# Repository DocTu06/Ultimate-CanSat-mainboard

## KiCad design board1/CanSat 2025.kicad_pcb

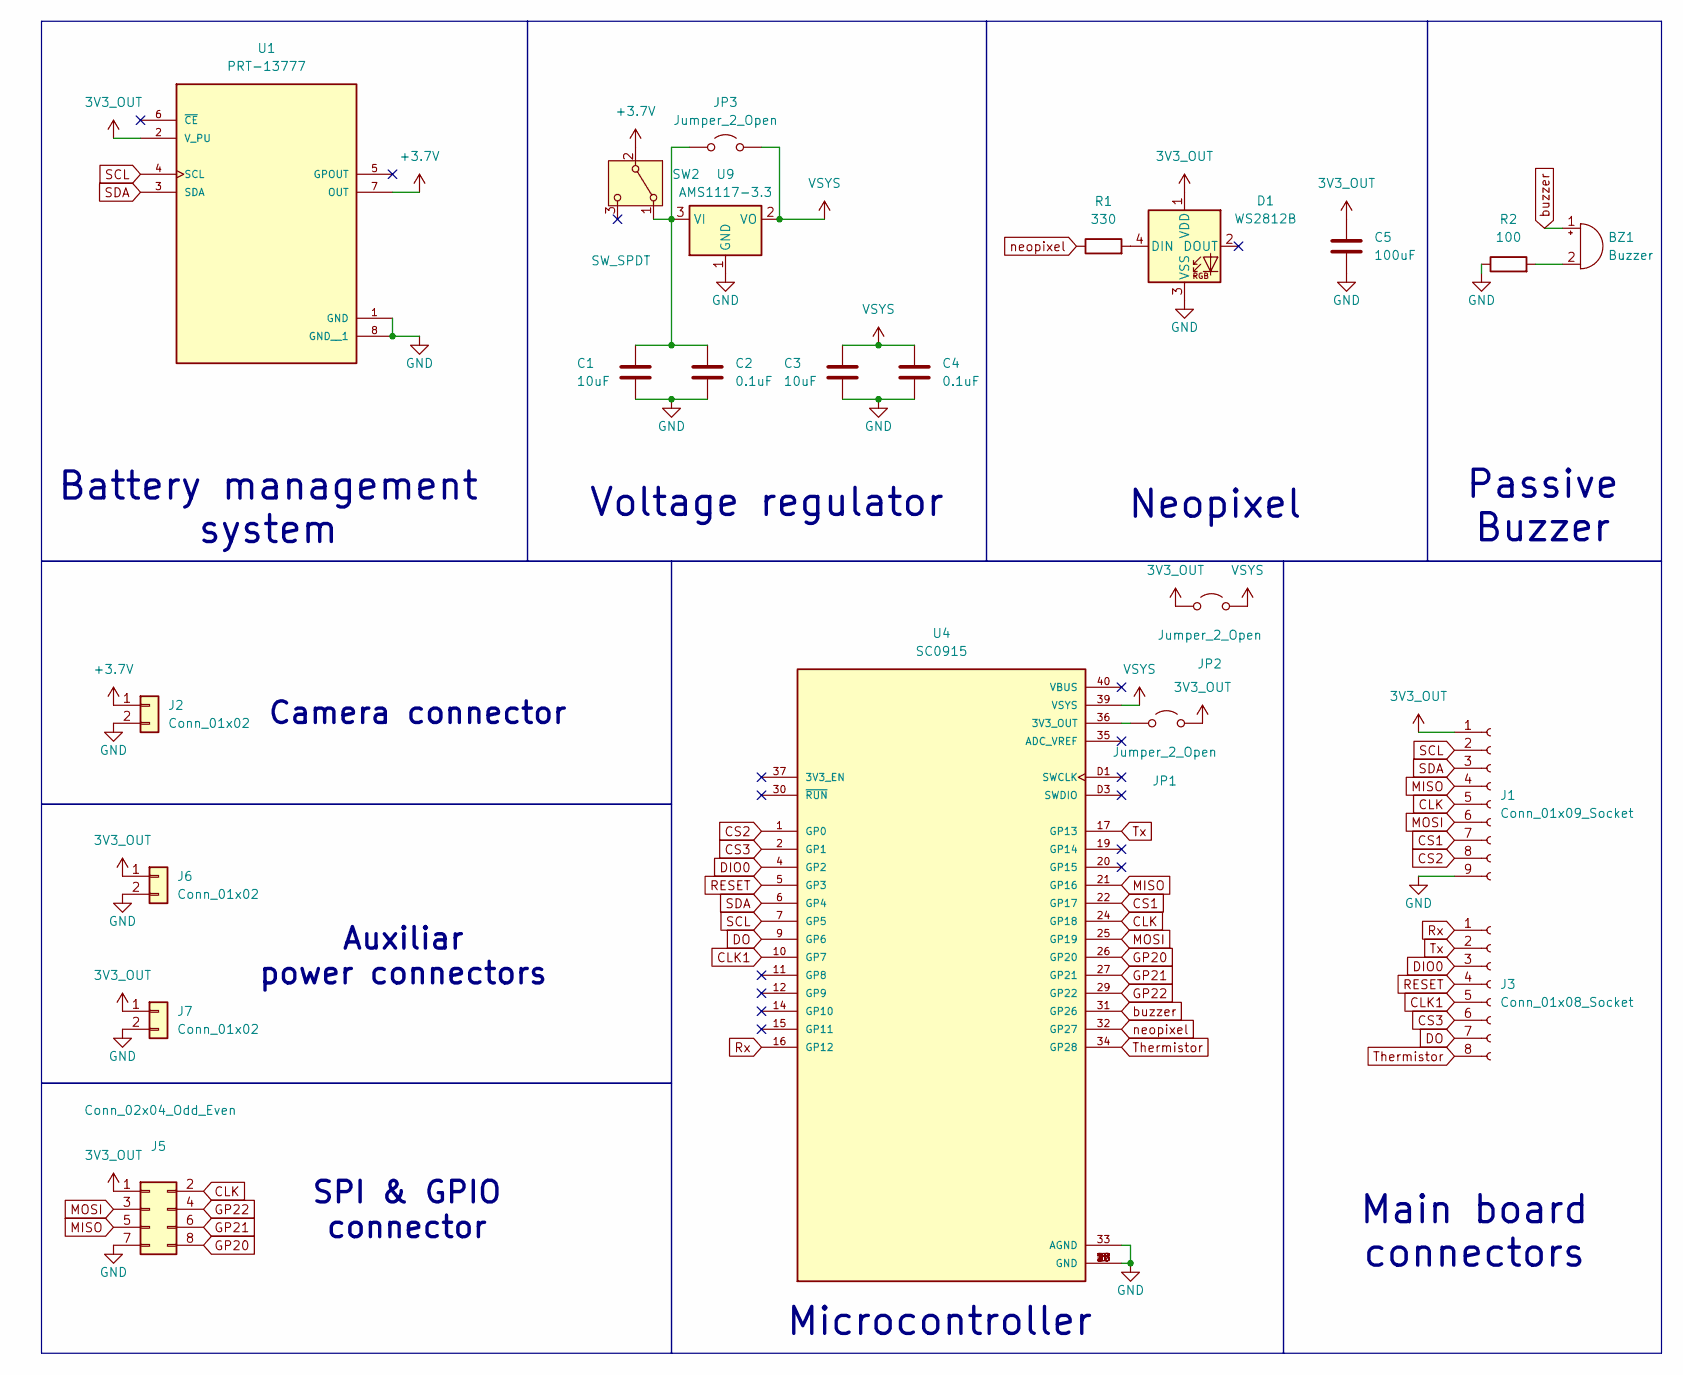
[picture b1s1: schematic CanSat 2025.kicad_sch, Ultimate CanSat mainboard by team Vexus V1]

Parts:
BZ1: Buzzer; Buzzer_pasiv
C1, C3: 10uF; C_0603_1608Metric_Pad1.08x0.95mm_HandSolder
C2, C4: 0.1uF; C_0603_1608Metric_Pad1.08x0.95mm_HandSolder
C5: 100uF; C_0603_1608Metric_Pad1.08x0.95mm_HandSolder
D1: WS2812B; LED_WS2812B_PLCC4_5.0x5.0mm_P3.2mm
J1: Conn_01x09_Socket; PinSocket_1x09_P2.54mm_Vertical
J2: Conn_01x02; Pad
J3: Conn_01x08_Socket; PinSocket_1x08_P2.54mm_Vertical
J5: Conn_02x04_Odd_Even; PinSocket_2x04_P2.54mm_Vertical
J6, J7: Conn_01x02; PinSocket_1x02_P2.54mm_Vertical
JP1, JP2, JP3: Jumper_2_Open; SolderJumper-2_P1.3mm_Open_TrianglePad1.0x1.5mm
R1: 330; R_0603_1608Metric_Pad0.98x0.95mm_HandSolder
R2: 100; R_0603_1608Metric_Pad0.98x0.95mm_HandSolder
SW2: SW_SPDT; SW_Slide_SPDT_Angled_CK_OS102011MA1Q
U1: PRT-13777; MODULE_PRT-13777; PARTREV v10
U4: SC0915; MODULE_SC0915; PARTREV 1.9
U9: AMS1117-3.3; SOT-223-3_TabPin2

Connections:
3V3_OUT: C5.1, D1.1 (VDD), J1.1, J5.1, J6.1, J7.1, JP1.2 (B), JP2.1 (A), U1.2 (V_PU)
+3.7V: J2.1, SW2.2 (B), U1.7 (OUT)
CLK: J1.5, J5.2, U4.24 (GP18)
CLK1: J3.5, U4.10 (GP7)
CS1: J1.7, U4.22 (GP17)
CS2: J1.8, U4.1 (GP0)
CS3: J3.6, U4.2 (GP1)
DIO0: J3.3, U4.4 (GP2)
DO: J3.7, U4.9 (GP6)
GND: C1.2, C2.2, C3.2, C4.2, C5.2, D1.3 (VSS), J1.9, J2.2, J5.7, J6.2, J7.2, R2.1, U1.1 (GND), U1.8 (GND__1), U4.3 (GND), U4.8 (GND), U4.13 (GND), U4.18 (GND), U4.23 (GND), U4.28 (GND), U4.33 (AGND), U4.38 (GND), U4.D2 (GND), U9.1 (GND)
GP20: J5.8, U4.26 (GP20)
GP21: J5.6, U4.27 (GP21)
GP22: J5.4, U4.29 (GP22)
MISO: J1.4, J5.5, U4.21 (GP16)
MOSI: J1.6, J5.3, U4.25 (GP19)
unnamed: BZ1.2 (-), R2.2
unnamed: D1.4 (DIN), R1.2
unnamed: JP1.1 (A), U4.36 (3V3_OUT)
unnamed: C1.1, C2.1, JP3.1 (A), SW2.1 (A), U9.3 (VI)
RESET: J3.4, U4.5 (GP3)
Rx: J3.1, U4.16 (GP12)
SCL: J1.2, U1.4 (SCL), U4.7 (GP5)
SDA: J1.3, U1.3 (SDA), U4.6 (GP4)
Thermistor: J3.8, U4.34 (GP28)
Tx: J3.2, U4.17 (GP13)
VSYS: C3.1, C4.1, JP2.2 (B), JP3.2 (B), U4.39 (VSYS), U9.2 (VO)
buzzer: BZ1.1 (+), U4.31 (GP26)
neopixel: R1.1, U4.32 (GP27)

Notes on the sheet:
Passive Buzzer
Voltage regulator
Microcontroller
Auxiliar power connectors
SPI & GPIO connector
Camera connector
Neopixel
Main board connectors
Battery management system

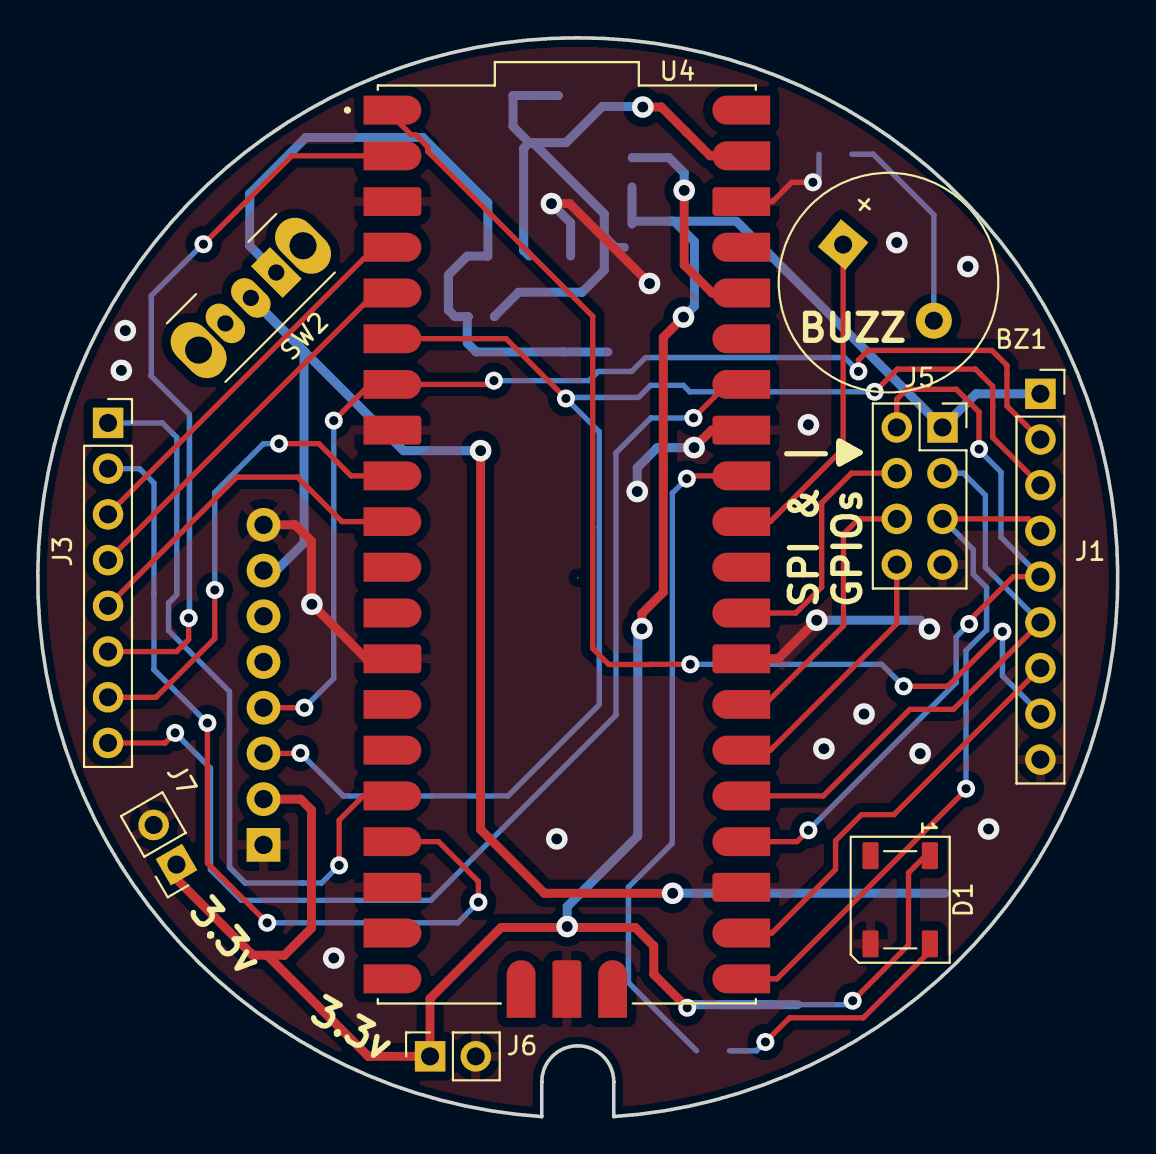
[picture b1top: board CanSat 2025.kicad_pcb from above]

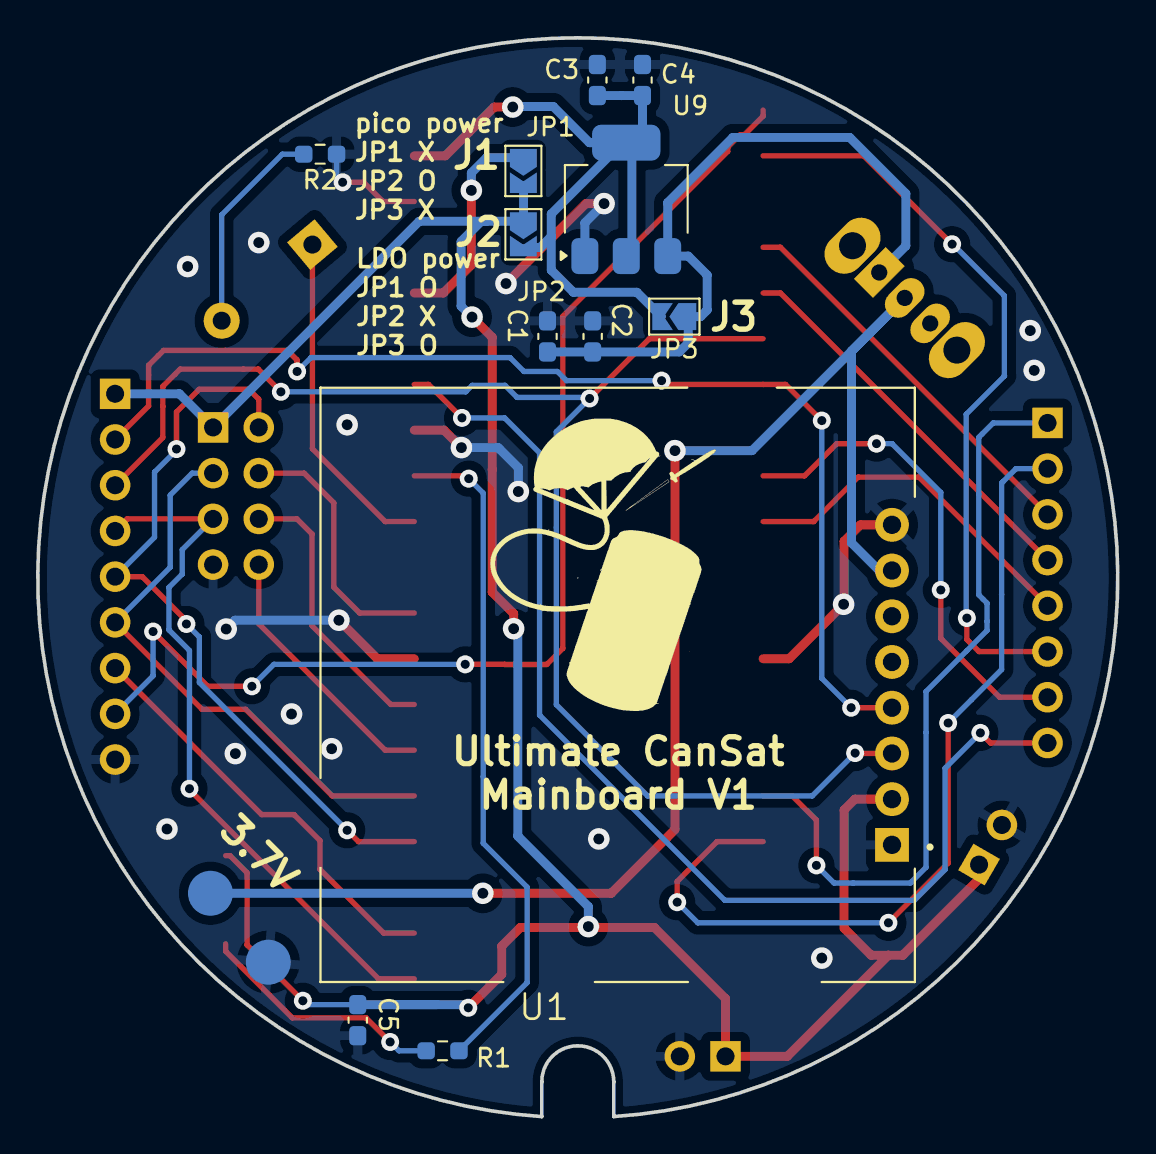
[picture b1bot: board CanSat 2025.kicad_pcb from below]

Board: 2 copper layers, 60.0 x 59.9 mm, 22 parts (13 on the bottom side), 28 nets.

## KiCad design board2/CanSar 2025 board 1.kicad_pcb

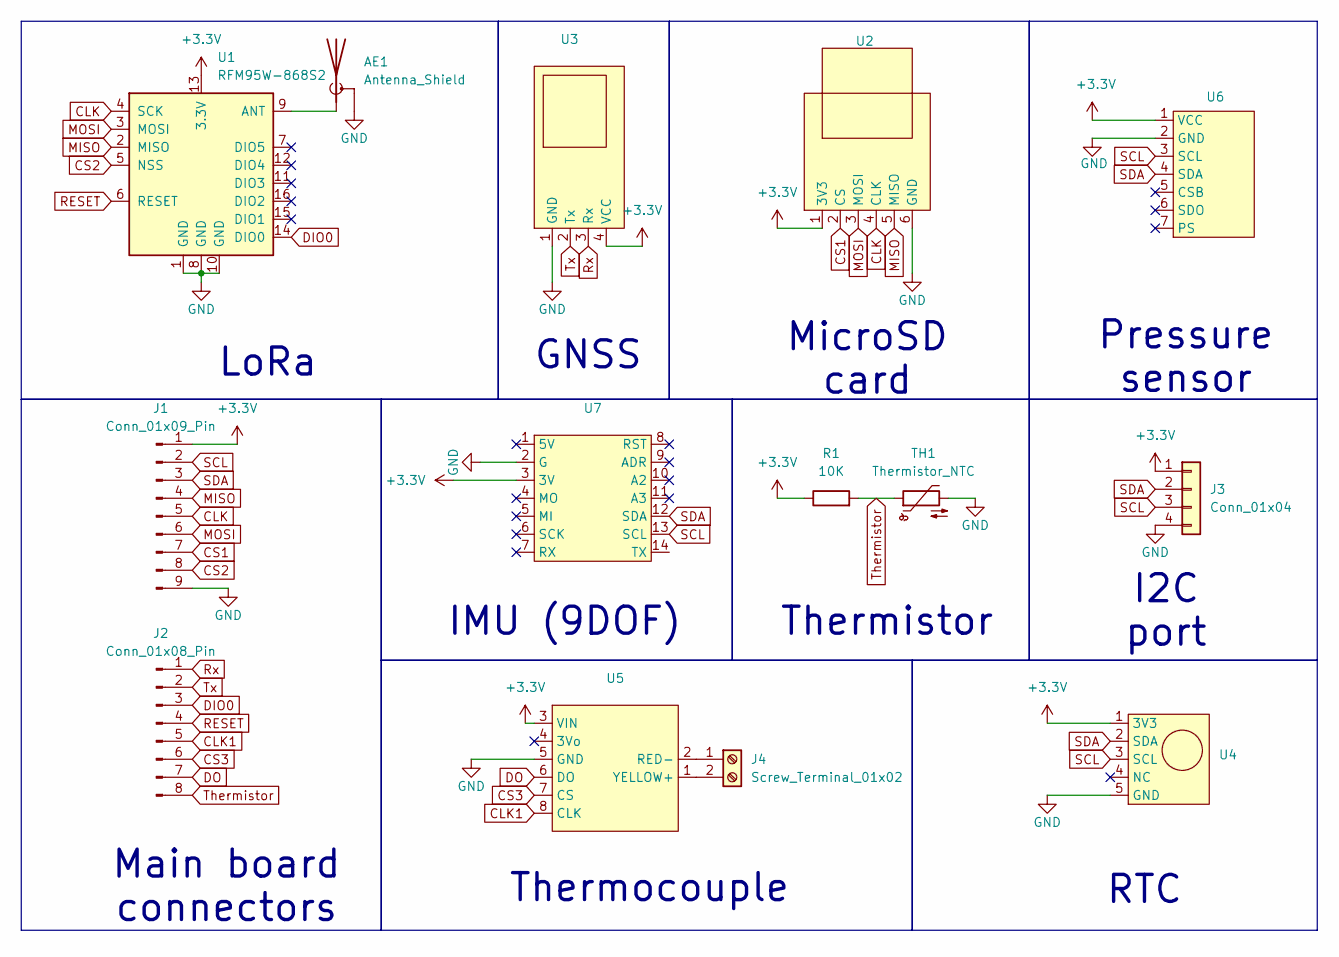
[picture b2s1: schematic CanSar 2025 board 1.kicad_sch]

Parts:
AE1: Antenna_Shield; PinHeader_1x02_P2.54mm_Vertical
J1: Conn_01x09_Pin; PinHeader_1x09_P2.54mm_Vertical
J2: Conn_01x08_Pin; PinHeader_1x08_P2.54mm_Vertical
J3: Conn_01x04; PinHeader_1x04_P2.54mm_Vertical
J4: Screw_Terminal_01x02; TerminalBlock_Phoenix_MKDS-1,5-2-5.08_1x02_P5.08mm_Horizont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
R1: 10K; R_Axial_DIN0207_L6.3mm_D2.5mm_P7.62mm_Horizontal
TH1: Thermistor_NTC; PinHeader_1x02_P2.54mm_Vertical
U1: RFM95W-868S2; HOPERF_RFM9XW_SMD
U2: MicroSd card
U3: PinHeader_1x04_P2.54mm_Vertical
U4: RTC
U5: Max31855
U6: MS5611
U7: BNO055+BMP280 adafruit

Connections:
+3.3V: J1.1, J3.1, R1.1, U1.13 (3.3V), U2.1 (3V3), U3.4 (VCC), U4.1 (3V3), U5.3 (VIN), U6.1 (VCC), U7.3 (3V)
CLK: J1.5, U1.4 (SCK), U2.4 (CLK)
CLK1: J2.5, U5.8 (CLK)
CS1: J1.7, U2.2 (CS)
CS2: J1.8, U1.5 (NSS)
CS3: J2.6, U5.7 (CS)
DIO0: J2.3, U1.14 (DIO0)
DO: J2.7, U5.6 (DO)
GND: AE1.2 (Shield), J1.9, J3.4, TH1.2, U1.1 (GND), U1.8 (GND), U1.10 (GND), U2.6 (GND), U3.1 (GND), U4.5 (GND), U5.5 (GND), U6.2 (GND), U7.2 (G)
MISO: J1.4, U1.2 (MISO), U2.5 (MISO)
MOSI: J1.6, U1.3 (MOSI), U2.3 (MOSI)
unnamed: AE1.1 (A), U1.9 (ANT)
unnamed: J4.1, U5.2 (RED-)
unnamed: J4.2, U5.1 (YELLOW+)
RESET: J2.4, U1.6 (RESET)
Rx: J2.1, U3.3 (Rx)
SCL: J1.2, J3.3, U4.3 (SCL), U6.3 (SCL), U7.13 (SCL)
SDA: J1.3, J3.2, U4.2 (SDA), U6.4 (SDA), U7.12 (SDA)
Thermistor: J2.8, R1.2, TH1.1
Tx: J2.2, U3.2 (Tx)

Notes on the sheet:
MicroSD card
GNSS
Main board connectors
Pressure sensor
RTC
IMU (9DOF)
LoRa
Thermocouple
I2C port
Thermistor

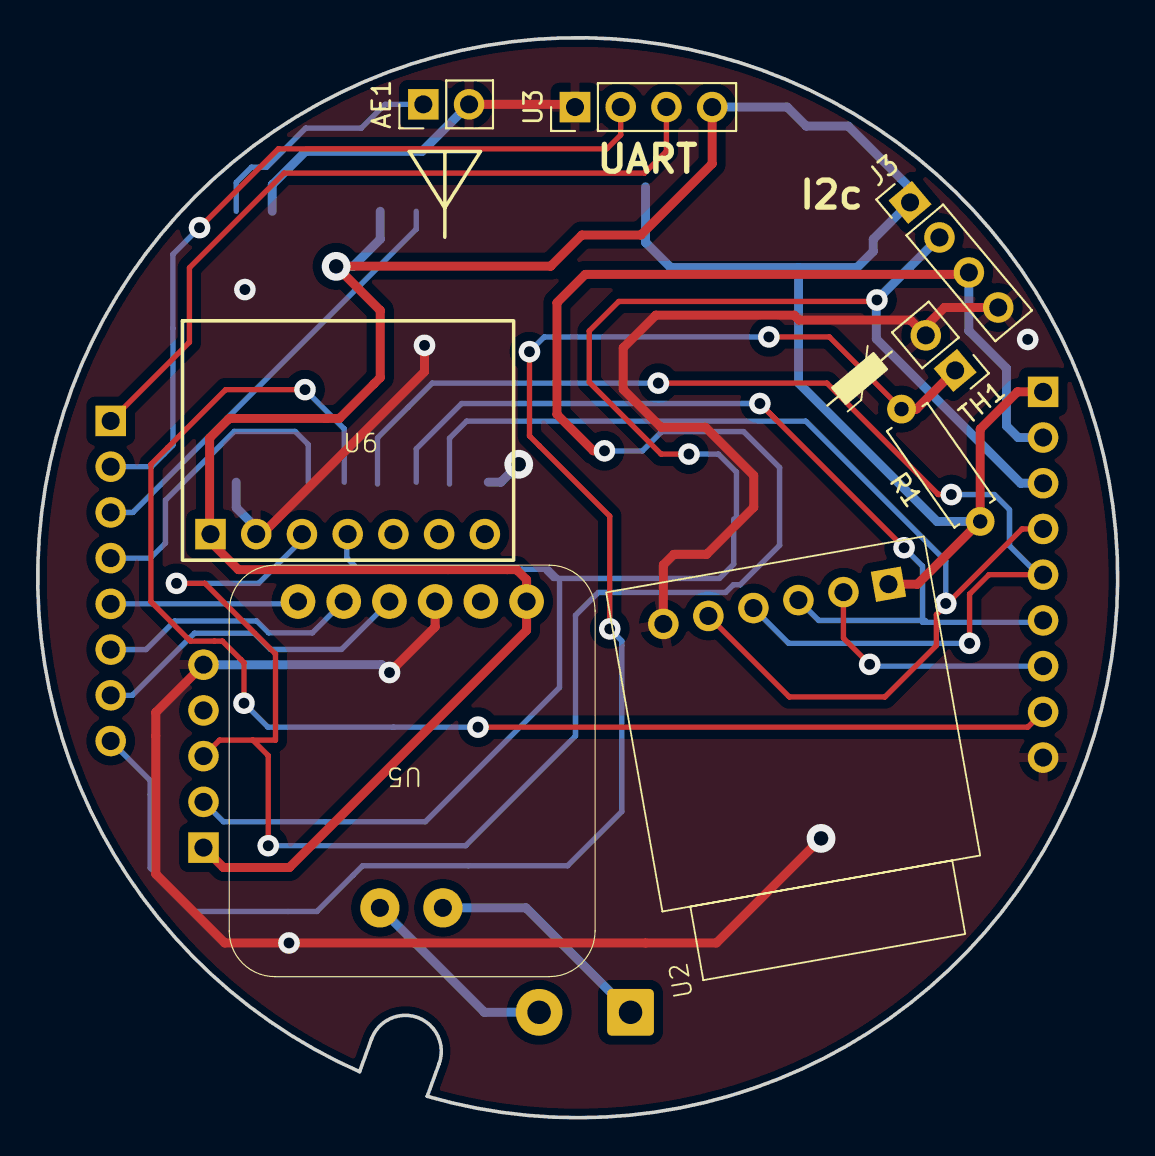
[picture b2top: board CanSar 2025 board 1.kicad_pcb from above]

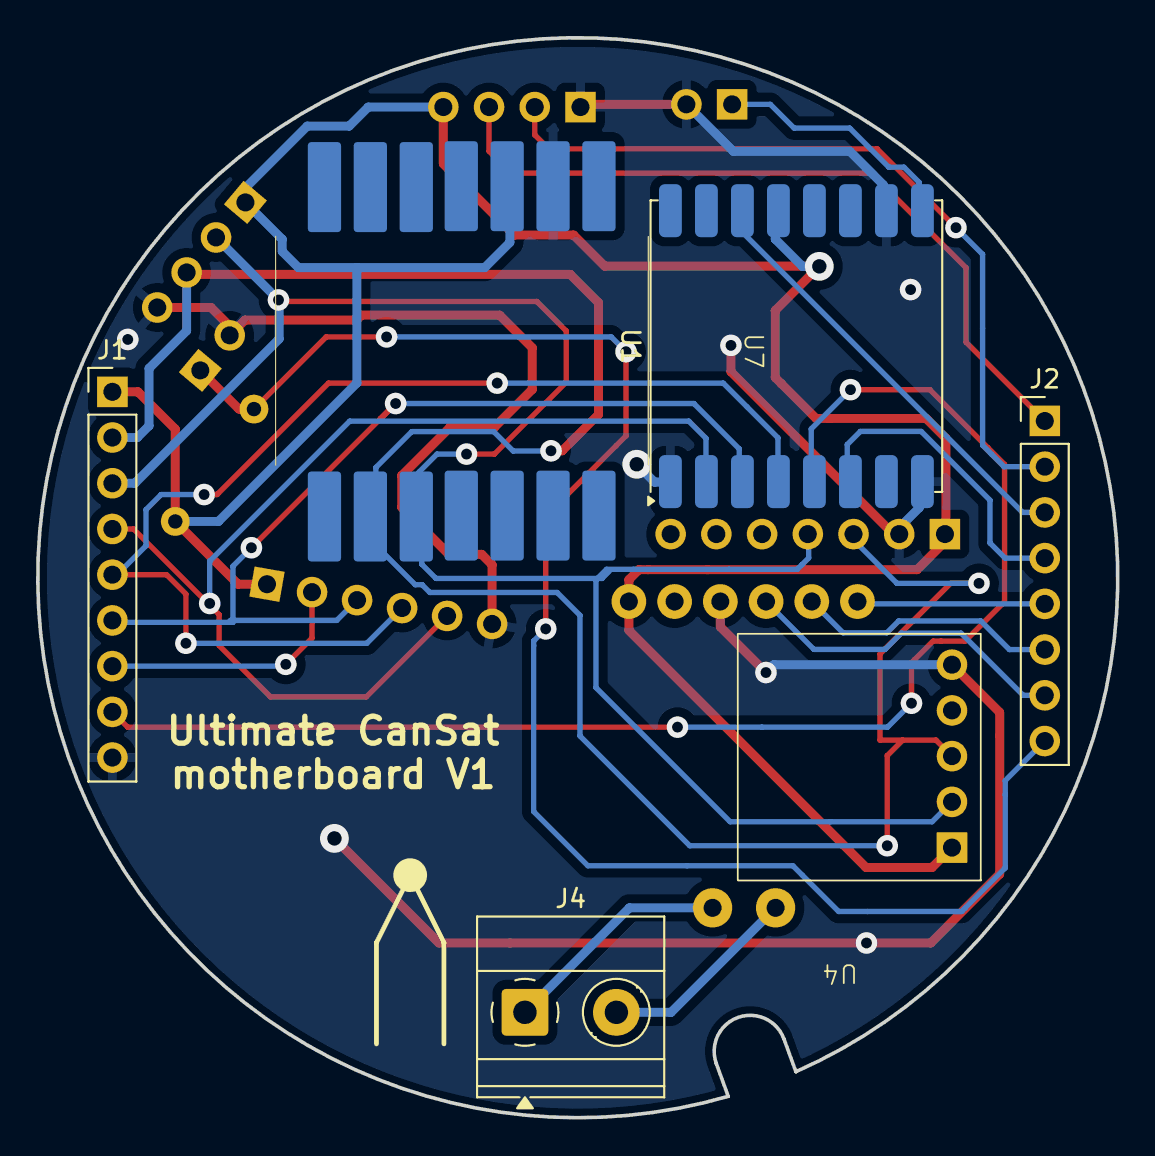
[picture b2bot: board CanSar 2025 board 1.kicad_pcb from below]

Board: 2 copper layers, 60.0 x 60.0 mm, 14 parts (6 on the bottom side), 20 nets.

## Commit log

2025-04-15 added boards
2025-04-15 Create LICENSE
